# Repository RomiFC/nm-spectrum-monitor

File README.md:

# :satellite: New Mexico Spectrum Monitor

The NMSM is a tool utilized by the NRAO-NM Interference Protection Group to identify and locate RF interference at the Very Large Array. It combines two previously separate systems: the Radio Frequency - Direction Finding System (RF-DFS) and Environmental Monitoring System (RF-EMS) into one combined spectrum monitor with omnidirectional and directional capabilities. The former is a 3-meter dish antenna with azimuth and elevation drives whereas the latter is a 50-foot tower with a nominally 0 dBi club antenna. Both RF chains are connected to a Keysight N9040B Spectrum Analyzer and are controlled by a Python GUI.

**Hardware:** Automation Direct P1AM-100 PLC with 15-point discrete output module, Parker Hannifin ACR9000 Motion Controller, 2 Aries AR-04AE Servo Drives, Keysight N9040B Spectrum Analyzer, and a Windows computer.

## 🏗️ Tech Stack

```mermaid
graph BT

    subgraph Hardware
    P1AM
    win[Windows Machine]
    ACR9000
    AR-04AE
    N9040B
    end

    subgraph Firmware
    C++
    AcroBASIC
    SCPI
    end

    subgraph client[Edge Client]
    Python([Python Front End])
    end

    subgraph Back End
    Database[(DRIFT<br>Database)]
    end

    C++ -->|Serial| Python
    AcroBASIC -->|Serial| Python
    SCPI -->|GPIB/LAN| Python

    P1AM --> C++
    win --> Python
    ACR9000 & AR-04AE --> AcroBASIC
    N9040B --> SCPI
    client --> Database
```

## 🚀 Deployment Requirements

- [NI-VISA](https://www.ni.com/en/support/downloads/drivers/download.ni-visa.html) or other suitable PyVISA backend.
- Ethernet, GPIB, serial, or other SCPI instrument connection.
  - [NI-488.2](https://www.ni.com/en/support/downloads/drivers/download.ni-488-2.html#484357) if using GPIB.

## 🛠️ Development Requirements

- All above requirements.
- [Python 3.11+](https://www.python.org/) and an understanding of the following:
  - [tkinter](https://docs.python.org/3/library/tkinter.html#module-tkinter)
  - [pySerial](https://pypi.org/project/pyserial/)
  - [PyVisa](https://pyvisa.readthedocs.io/en/latest/)
  - [matplotlib](https://matplotlib.org/)
- Suitable Python IDE (Recommended [VSCode](https://code.visualstudio.com/))
- Python packager (Recommended [PyInstaller](https://pyinstaller.org/en/stable/))
- [PlatformIO](https://platformio.org/) for updating PLC firmware.

> [!NOTE]
> Freezing tools (Such as PyInstaller) package the entire Python Interpreter and installed libraries which generates large executables and could be flagged as a virus. It is recommended to create a virtual environment and only install/package the libraries used in the program. These executables will also only work on the OS that built them (A Windows deployment must be built on a Windows computer).

### Packages

```bash
pip install -r requirements.txt
```

## :mailbox: Authors

- [Remy Nguyen](https://github.com/RomiFC)
- [Natalie Ceonzo](https://github.com/nceonzo)
- [Hina Suzuki](https://github.com/hina18201716)

<picture>
  <source media="(prefers-color-scheme: dark)" srcset="https://public.nrao.edu/wp-content/uploads/2023/02/logoGroupWhite.png">
  <source media="(prefers-color-scheme: light)" srcset="https://public.nrao.edu/wp-content/uploads/2023/02/logoGroupColor.png">
  
</picture>

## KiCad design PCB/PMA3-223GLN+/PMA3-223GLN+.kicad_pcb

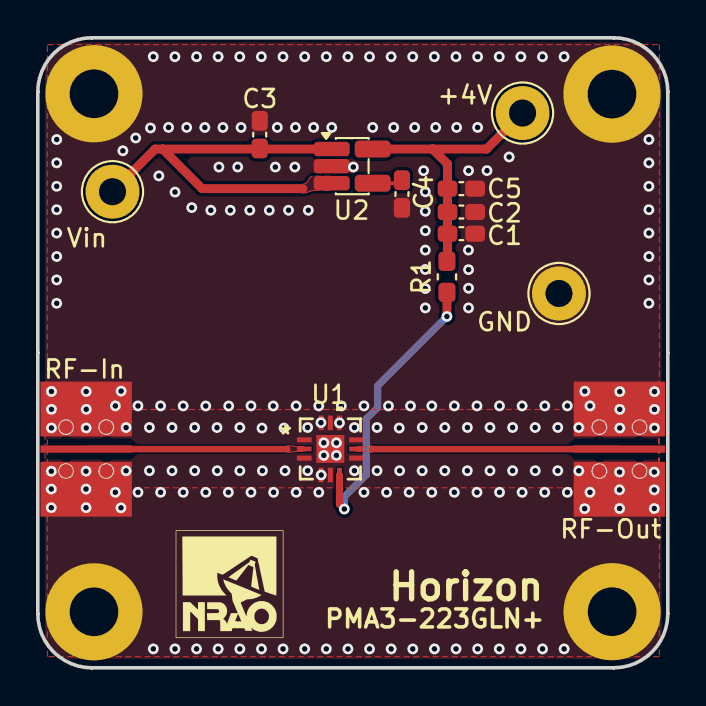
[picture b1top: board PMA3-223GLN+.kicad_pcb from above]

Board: 4 copper layers, 35.0 x 35.0 mm, 14 parts (0 on the bottom side), 7 nets.

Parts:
+4V: +4V; TestPoint_Loop_D2.54mm_Drill1.5mm_Beaded
C1: 5p; C_0402_1005Metric_Pad0.74x0.62mm_HandSolder
C2: 0.1u; C_0402_1005Metric_Pad0.74x0.62mm_HandSolder
C3: 1u; C_0402_1005Metric_Pad0.74x0.62mm_HandSolder
C4: 100p; C_0402_1005Metric_Pad0.74x0.62mm_HandSolder
C5: 2.2u; C_0402_1005Metric_Pad0.74x0.62mm_HandSolder
G**: NRAO Logo; nrao_logo_silk
GND: GND; TestPoint_Loop_D2.54mm_Drill1.5mm_Beaded
J1, J2: Conn_Coaxial; BU-1420761881
R1: 18; C_0603_1608Metric_Pad1.08x0.95mm_HandSolder
U1: PMA3-223GLN+; DQ1225_MNC
U2: AP2210N-4.0TRG1; SOT-23-5
Vin: Vin; TestPoint_Loop_D2.54mm_Drill1.5mm_Beaded

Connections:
+4V: +4V.1 (1_1), C1.1, C2.1, C5.1, R1.2, U2.5 (VOUT)
GND: C1.2, C2.2, C3.2, C4.2, C5.2, GND.1 (1_1), J1.2 (Ext), J2.2 (Ext), U1.1 (GND), U1.3 (GND), U1.4 (NC), U1.5 (NC), U1.7 (GND), U1.9 (GND), U1.10 (NC), U1.11 (NC), U1.12 (NC), U1.13 (PADDLE), U2.2 (GND)
unnamed: C4.1, U2.4 (BP)
RF_IN: J1.1 (In), U1.2 (RF-IN)
RF_OUT: J2.1 (In), U1.8 (RF-OUT/DC-IN)
VDC: C3.1, U2.1 (VIN), U2.3 (ON/~OFF), Vin.1 (1_1)
VDD: R1.1, U1.6 (VDD)

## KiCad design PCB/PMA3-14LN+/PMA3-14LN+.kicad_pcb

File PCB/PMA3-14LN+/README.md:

# PMA3-14LN+ Changelog

## Revision C - 6/8/2026

### Added

- New thermal via grid underneath U2 for temperature management
- Layer 2 DGS underneath L1,L2,C1,C2,C3,C4 as follows:
    - Shunts L1,L2,C3,C4: 0.60mm x 0.1mm (trace pad)
    - Series C1,C2: 1.5mm x 0.5mm

### Changed

- Changed mouting pad dimensions of L1,L2,C1,C2,C3,C4 to 0.56mm x 0.62mm rounded rectangle. Previous values:
    - Shunts L1,L2: 0.37mm x 0.72mm rounded rectangle (trace pad) and 0.59mm x 0.64mm rectangle (bias pad)
    - Series C1,C2: 0.56mm x 0.37mm rounded rectangle (both)
    - Shunts C3,C4: 0.37mm x 0.72mm (trace pad) and 0.56mm x 0.62mm (bias pad)
- Increased clearance around trace components from 0.2mm to 0.3mm

## Revision B - 10/24/2023

### Added

- More PTH vias around and directly under RF components.
- Another layer of via picketing around transmission line.
- Silkscreen revision indicator.
- Dimensioning to assembly drawing.

### Changed

- Removed Hammond 1554B compatibility due to difficulties in assembly and weatherproofing SMA connectors. Overall board is smaller at 35mm x 35mm.
- SMA Connectors replaced with Mueller BU-1420761881 which have an upper frequency of 26.5 GHz and better impedance matching at the landing.
- GCPW dimensions from w = 0.415mm, s = 0.6mm, to w = 0.37mm, s = 0.2mm and added 0.375mm taper from SMA clearance to GCPW clearance.

### Fixed

- C9 footprint now correctly matches schematic (0402 --> 1206).
- Moved SMA footprints closer to board edge to reduce filing prior to assembly.

## Revision A - 4/12/2023

### First revision 🎉🎉🎉

- Board is built to 4-layer OSHPark specifications
- This amplifier showed slightly lower gain than expected, rolling off quicker with frequency. This is likely due to the SMA connector landings which had a known impedance mismatch, resulting in a steep rolloff somewhere between 12 and 18 GHz.

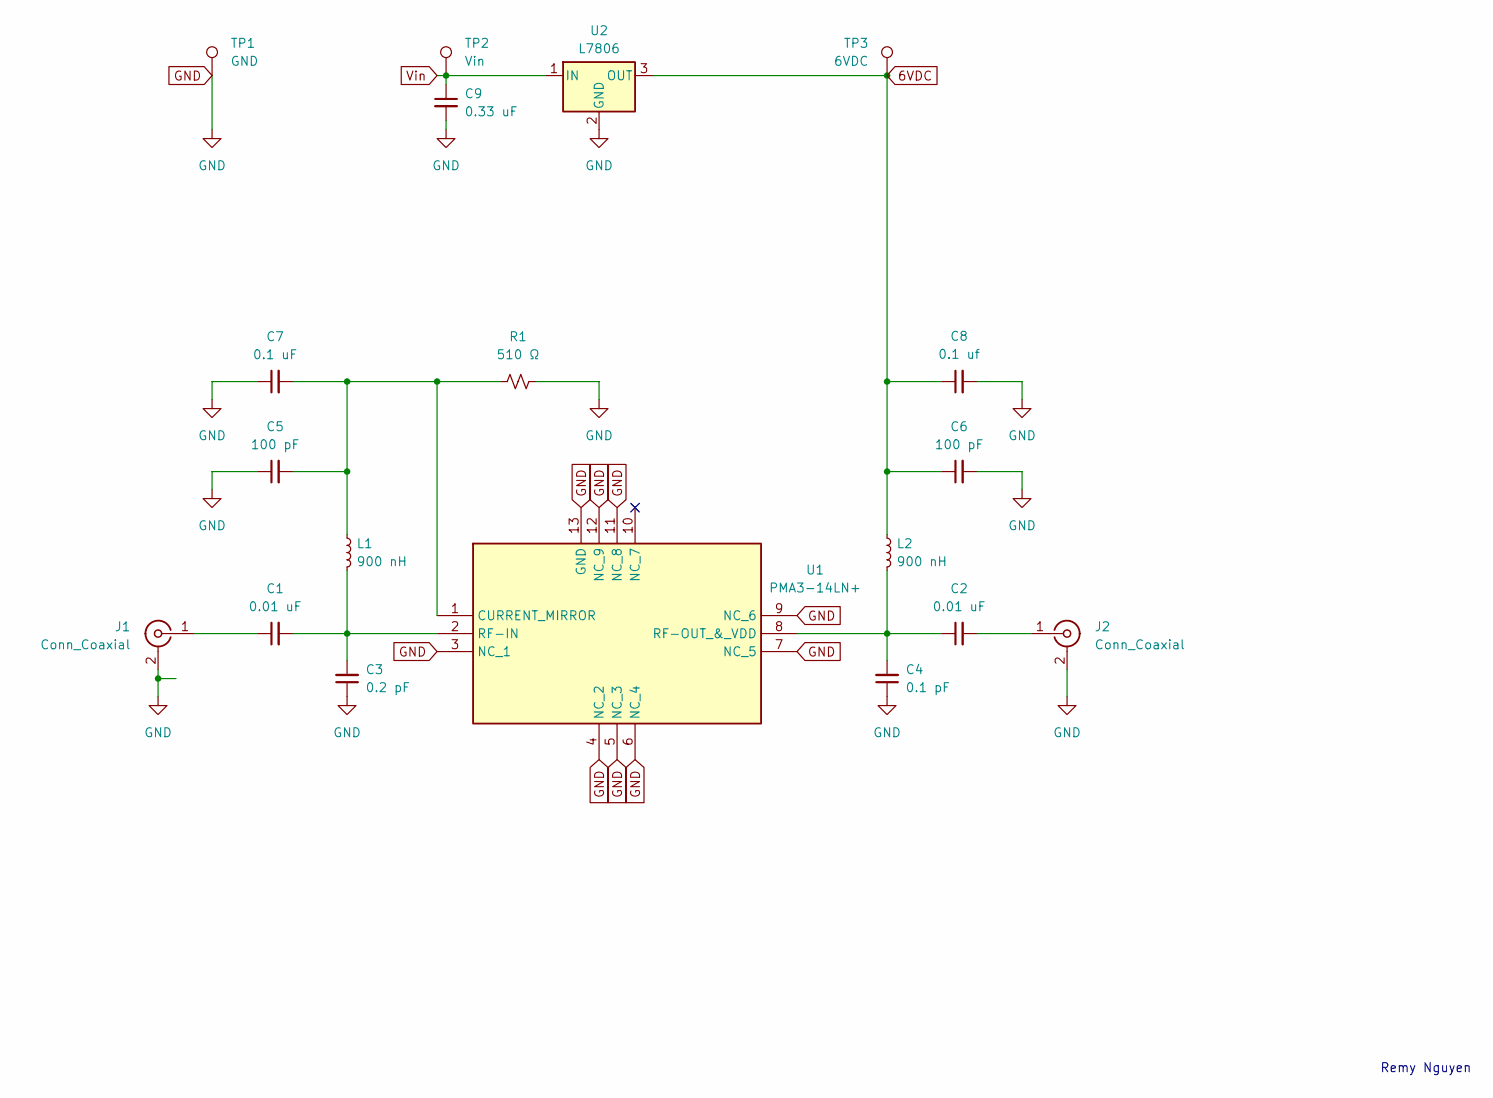
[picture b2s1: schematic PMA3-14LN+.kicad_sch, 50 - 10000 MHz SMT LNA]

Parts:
C1, C2: 0.01 uF; C_0402_1005Metric
C3: 0.2 pF; C_0402_1005Metric
C4: 0.1 pF; C_0402_1005Metric
C5, C6: 100 pF; C_0402_1005Metric
C7: 0.1 uF; C_0402_1005Metric
C8: 0.1 uf; C_0402_1005Metric
C9: 0.33 uF; C_0402_1005Metric
J1, J2: Conn_Coaxial; Mueller BU-1420761881-RevB
L1, L2: 900 nH; L_0402_1005Metric
R1: 510 Ω; R_0402_1005Metric
TP1: GND; TestPoint_Loop_D2.54mm_Drill1.5mm_Beaded
TP2: Vin; TestPoint_Loop_D2.54mm_Drill1.5mm_Beaded
TP3: 6VDC; TestPoint_Loop_D2.54mm_Drill1.5mm_Beaded
U1: PMA3-14LN+; QFN51P300X300X89-13N; Mouser Part Number 139-PMA3-14LN+
U2: L7806; TO-263-2

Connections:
6VDC: C6.1, C8.1, L2.1, TP3.1, U2.3 (OUT)
GND: C3.1, C4.1, C5.1, C6.2, C7.1, C8.2, C9.2, J1.2 (Ext), J2.2 (Ext), R1.2, TP1.1, U1.3 (NC_1), U1.4 (NC_2), U1.5 (NC_3), U1.6 (NC_4), U1.7 (NC_5), U1.9 (NC_6), U1.11 (NC_8), U1.12 (NC_9), U1.13 (GND), U2.2 (GND)
unnamed: C5.2, C7.2, L1.1, R1.1, U1.1 (CURRENT_MIRROR)
unnamed: C1.2, C3.2, L1.2, U1.2 (RF-IN)
unnamed: C2.1, C4.2, L2.2, U1.8 (RF-OUT_&_VDD)
unnamed: C1.1, J1.1 (In)
unnamed: C2.2, J2.1 (In)
Vin: C9.1, TP2.1, U2.1 (IN)

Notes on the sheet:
Remy Nguyen

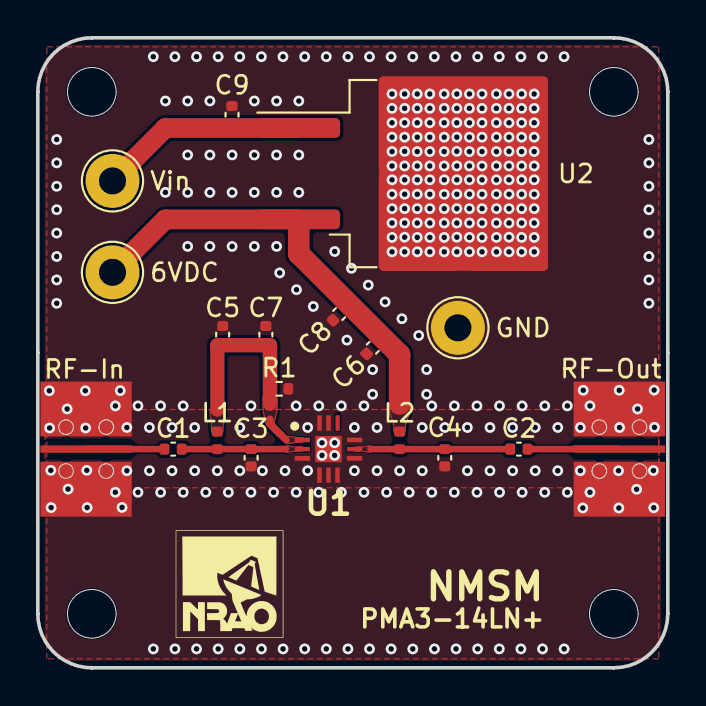
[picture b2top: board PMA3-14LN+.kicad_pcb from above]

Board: 4 copper layers, 35.0 x 35.0 mm, 20 parts (0 on the bottom side), 8 nets.

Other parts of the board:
 : FabDrawing-4Layer-Metric-Compact-OSH

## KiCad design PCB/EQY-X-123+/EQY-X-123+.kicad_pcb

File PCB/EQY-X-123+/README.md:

# EQY-X-123+ X-db Equalizer Changelog

## Revision A - 6/29/2026

### First revision 🎉🎉🎉

- Board is built to 4-layer OSHPark specifications
- Will update when board has been fabricated and assembled

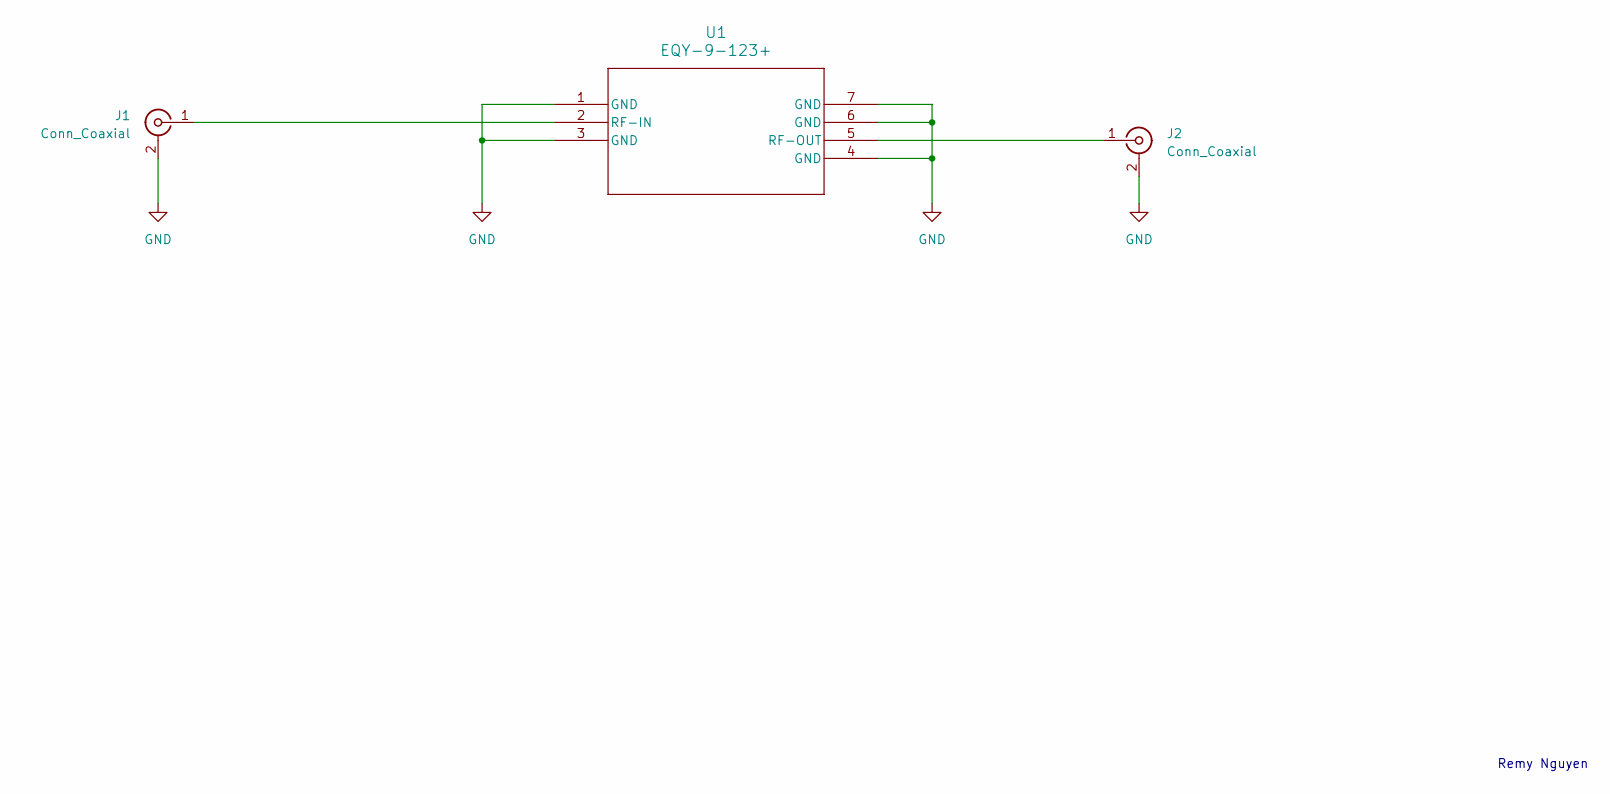
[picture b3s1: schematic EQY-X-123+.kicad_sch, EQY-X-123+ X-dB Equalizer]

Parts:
J1, J2: Conn_Coaxial; Mueller BU-1420761881-RevB
U1: EQY-9-123+; KC3011

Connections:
GND: J1.2 (Ext), J2.2 (Ext), U1.1 (GND), U1.3 (GND), U1.4 (GND), U1.6 (GND), U1.7 (GND)
unnamed: J1.1 (In), U1.2 (RF-IN)
unnamed: J2.1 (In), U1.5 (RF-OUT)

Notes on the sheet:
Remy Nguyen

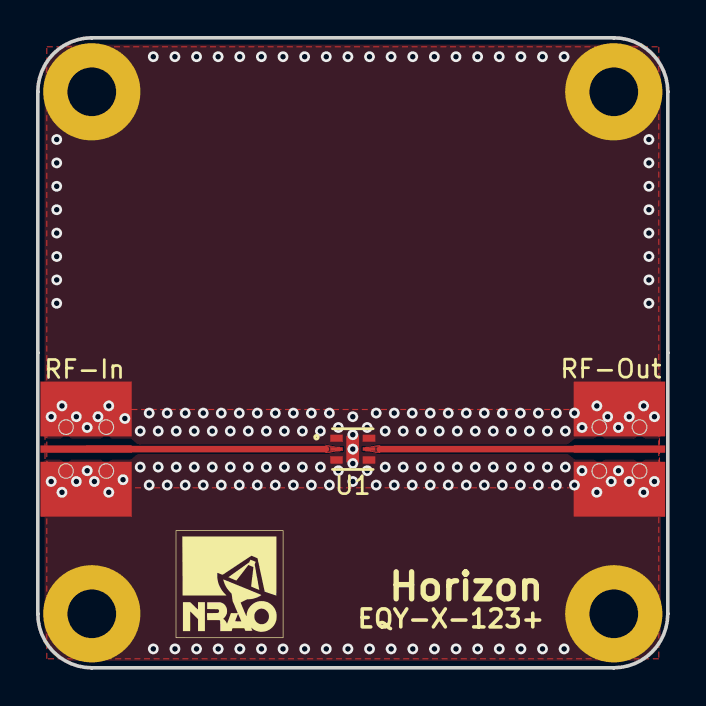
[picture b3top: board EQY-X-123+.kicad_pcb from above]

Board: 4 copper layers, 35.0 x 35.0 mm, 4 parts (0 on the bottom side), 3 nets.

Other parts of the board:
 : FabDrawing-4Layer-Metric-Compact-OSH

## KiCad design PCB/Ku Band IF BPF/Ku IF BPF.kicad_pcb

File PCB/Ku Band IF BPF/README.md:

# 1 - 9 GHz Bandpass Filter Changelog

## Revision A - 6/29/2026

### First revision 🎉🎉🎉

- Board is built to 4-layer OSHPark specifications
- Will update when board has been fabricated and assembled

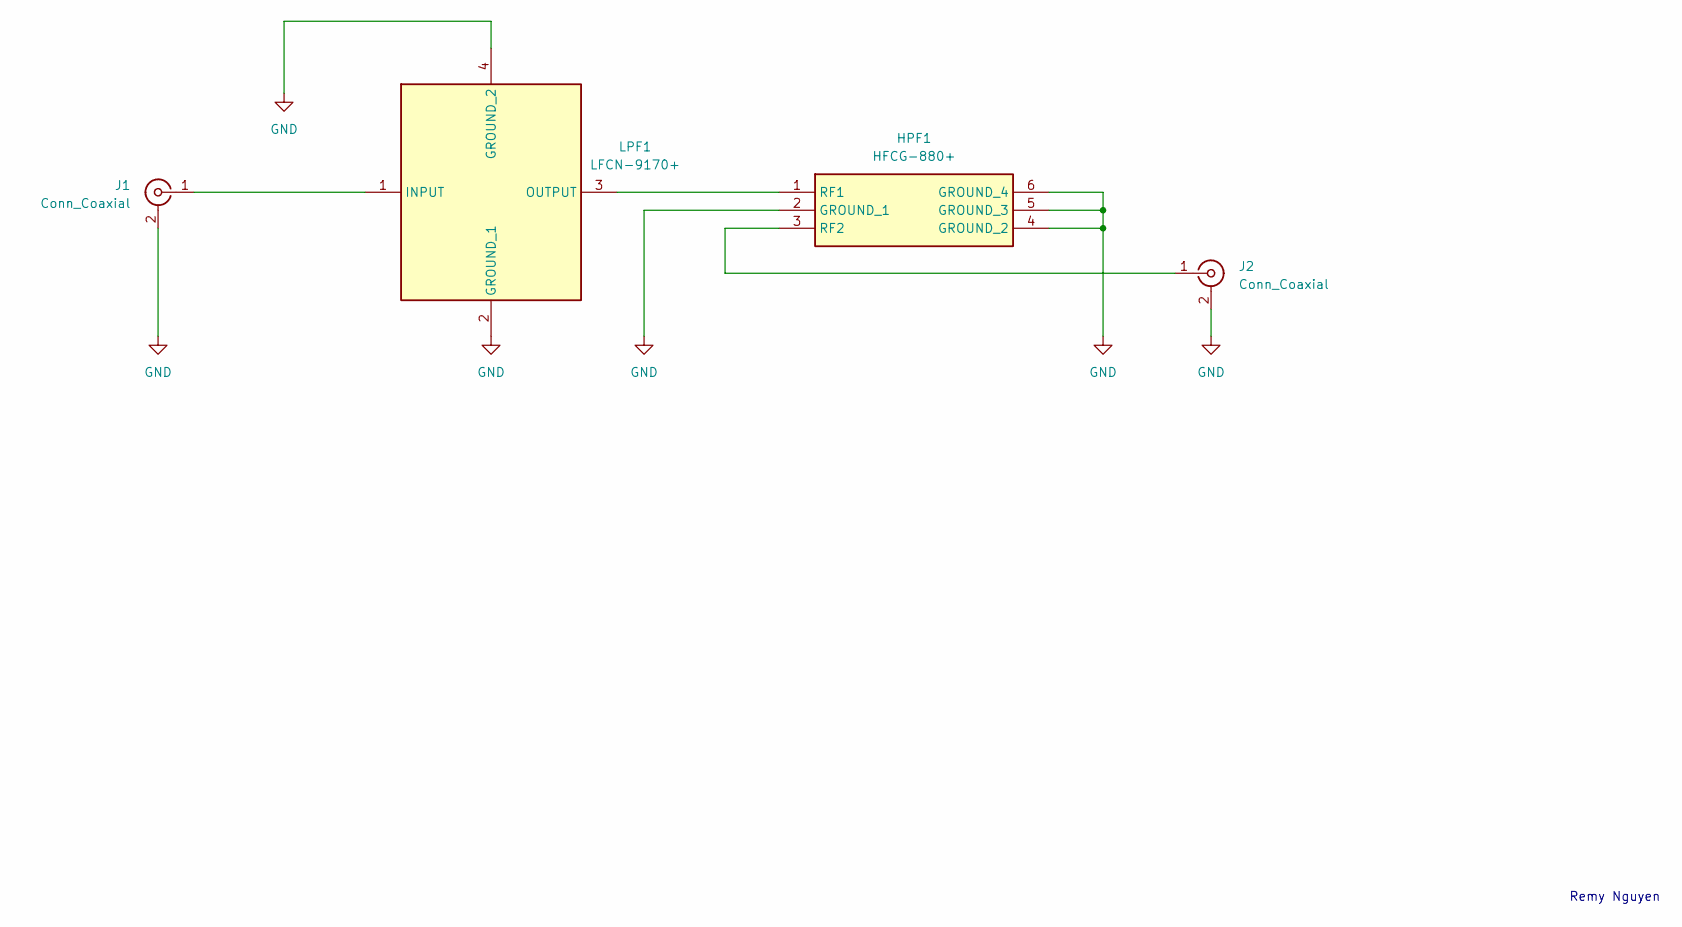
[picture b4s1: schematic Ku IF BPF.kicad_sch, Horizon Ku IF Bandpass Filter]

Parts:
HPF1: HFCG-880+; HFCG880; Mouser Part Number 139-HFCG-880+
J1, J2: Conn_Coaxial; Mueller BU-1420761881-RevB
LPF1: LFCN-9170+; LFCN9170; Mouser Part Number 139-LFCN-9170

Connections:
GND: HPF1.2 (GROUND_1), HPF1.4 (GROUND_2), HPF1.5 (GROUND_3), HPF1.6 (GROUND_4), J1.2 (Ext), J2.2 (Ext), LPF1.2 (GROUND_1), LPF1.4 (GROUND_2)
unnamed: HPF1.1 (RF1), LPF1.3 (OUTPUT)
unnamed: HPF1.3 (RF2), J2.1 (In)
unnamed: J1.1 (In), LPF1.1 (INPUT)

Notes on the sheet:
Remy Nguyen

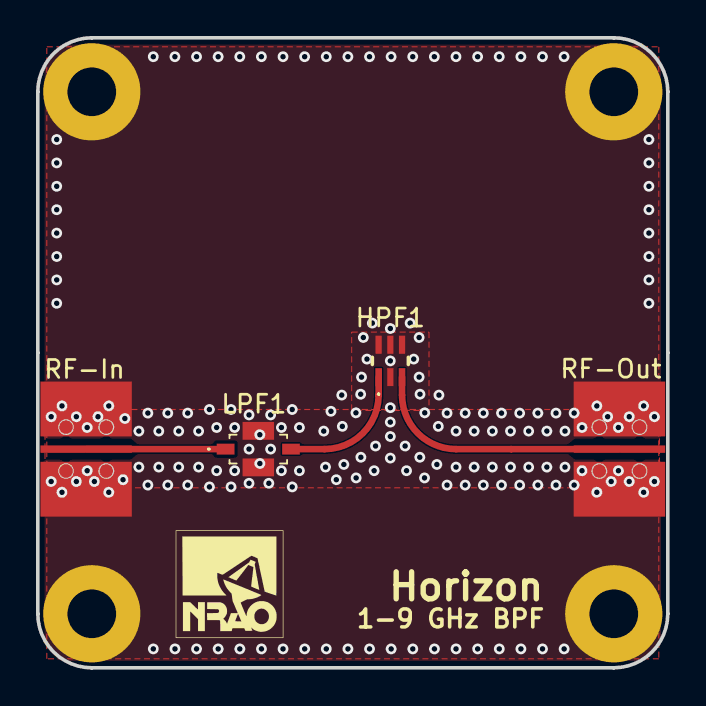
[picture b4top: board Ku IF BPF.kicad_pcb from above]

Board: 4 copper layers, 35.0 x 35.0 mm, 5 parts (0 on the bottom side), 4 nets.

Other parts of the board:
 : FabDrawing-4Layer-Metric-Compact-OSH

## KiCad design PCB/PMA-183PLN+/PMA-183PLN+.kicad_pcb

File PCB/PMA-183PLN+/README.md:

# PMA-183PLN+ Changelog

## Revision B - 7/5/2023

### Added

- More PTH vias around and directly under RF components.
- Another layer of via picketing around transmission line.
- Silkscreen revision indicator.
- Dimensioning to assembly drawing.

### Changed

- Removed Hammond 1554B compatibility due to difficulties in assembly and weatherproofing SMA connectors.
- GCPW dimensions from w = 0.41mm, s = 0.2mm, to w = 0.37mm, s = 0.2mm and added 0.375mm taper from SMA clearance to GCPW clearance.

### Fixed

- C9 footprint now correctly matches schematic (0402 --> 1206).
- Moved SMA footprints closer to board edge to reduce filing prior to assembly.

## Revision A - 6/12/2023

### First revision 🎉🎉🎉

- Board is built to 4-layer OSHPark specifications
- Testing shows amplifier oscillates strongly at ~18.5 GHz. This occurs both when the amplifier is biased through the regulator or directly from a DC power supply. SMA landings were also copied from test coupons so that can likely be ruled out. This is possibly due to the lack of PTH vias directly under the IC or the tuning/spacing of picketing around the transmission line.

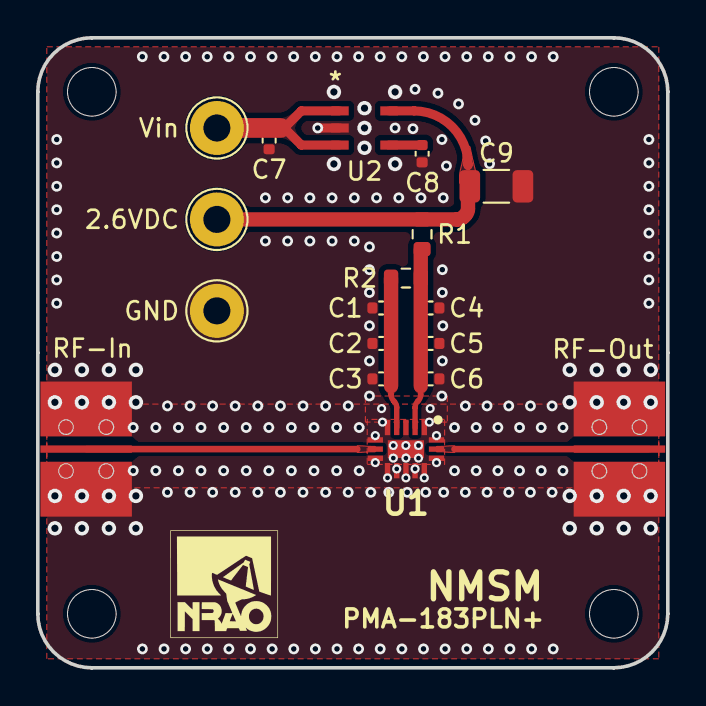
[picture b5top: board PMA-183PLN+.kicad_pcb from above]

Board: 4 copper layers, 35.0 x 35.0 mm, 20 parts (0 on the bottom side), 8 nets.

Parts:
 : FabDrawing-4Layer-Metric-Compact-OSH
 #2: LOGO; GCPW_osh3_90mm_user
C1, C4, C7: 0.33 uF; C_0402_1005Metric
C2, C5: 1000 pF; C_0402_1005Metric
C3, C6: 100 pF; C_0402_1005Metric
C8: 470 pF; C_0402_1005Metric
C9: 2.2 uF; C_1206_3216Metric
J1, J2: Conn_Coaxial; Mueller BU-1420761881
R1: 10 Ω; R_0603_1608Metric
R2: 180 Ω; R_0603_1608Metric
TP1: GND; TestPoint_Loop_D2.54mm_Drill1.5mm_Beaded
TP2: Vin; TestPoint_Loop_D2.54mm_Drill1.5mm_Beaded
TP3: 2.6VDC; TestPoint_Loop_D2.54mm_Drill1.5mm_Beaded
U1: PMA-183PLN+; QFN51P250X350X85-17N
U2: MIC5219-2.6YM5-TR; SOT-23-5_M5_MCH

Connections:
2.6VDC: C9.1, R1.2, TP3.1, U2.5 (OUT)
GND: C1.1, C2.1, C3.1, C4.2, C5.2, C6.2, C7.2, C8.2, C9.2, J1.2 (Ext), J2.2 (Ext), TP1.1, U1.1 (NC_1), U1.3 (NC_2), U1.5 (NC_3), U1.6 (GND_1), U1.8 (GND_2), U1.9 (NC_4), U1.10 (NC_5), U1.11 (NC_6), U1.12 (NC_7), U1.13 (NC_8), U1.14 (GND_3), U1.16 (GND_4), U1.17 (EP), U2.2 (GND)
unnamed: J1.1 (In), U1.7 (RF-IN)
unnamed: J2.1 (In), U1.15 (RF-OUT)
unnamed: C4.1, C5.1, C6.1, R1.1, R2.2, U1.2 (VDD)
unnamed: C1.2, C2.2, C3.2, R2.1, U1.4 (VE)
unnamed: C8.1, U2.4 (BYP)
Vin: C7.1, TP2.1, U2.1 (IN), U2.3 (EN)

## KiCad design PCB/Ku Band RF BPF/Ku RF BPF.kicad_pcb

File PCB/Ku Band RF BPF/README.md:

# 10 - 18 GHz Bandpass Filter Changelog

## Revision A - 6/29/2026

### First revision 🎉🎉🎉

- Board is built to 4-layer OSHPark specifications
- Will update when board has been fabricated and assembled

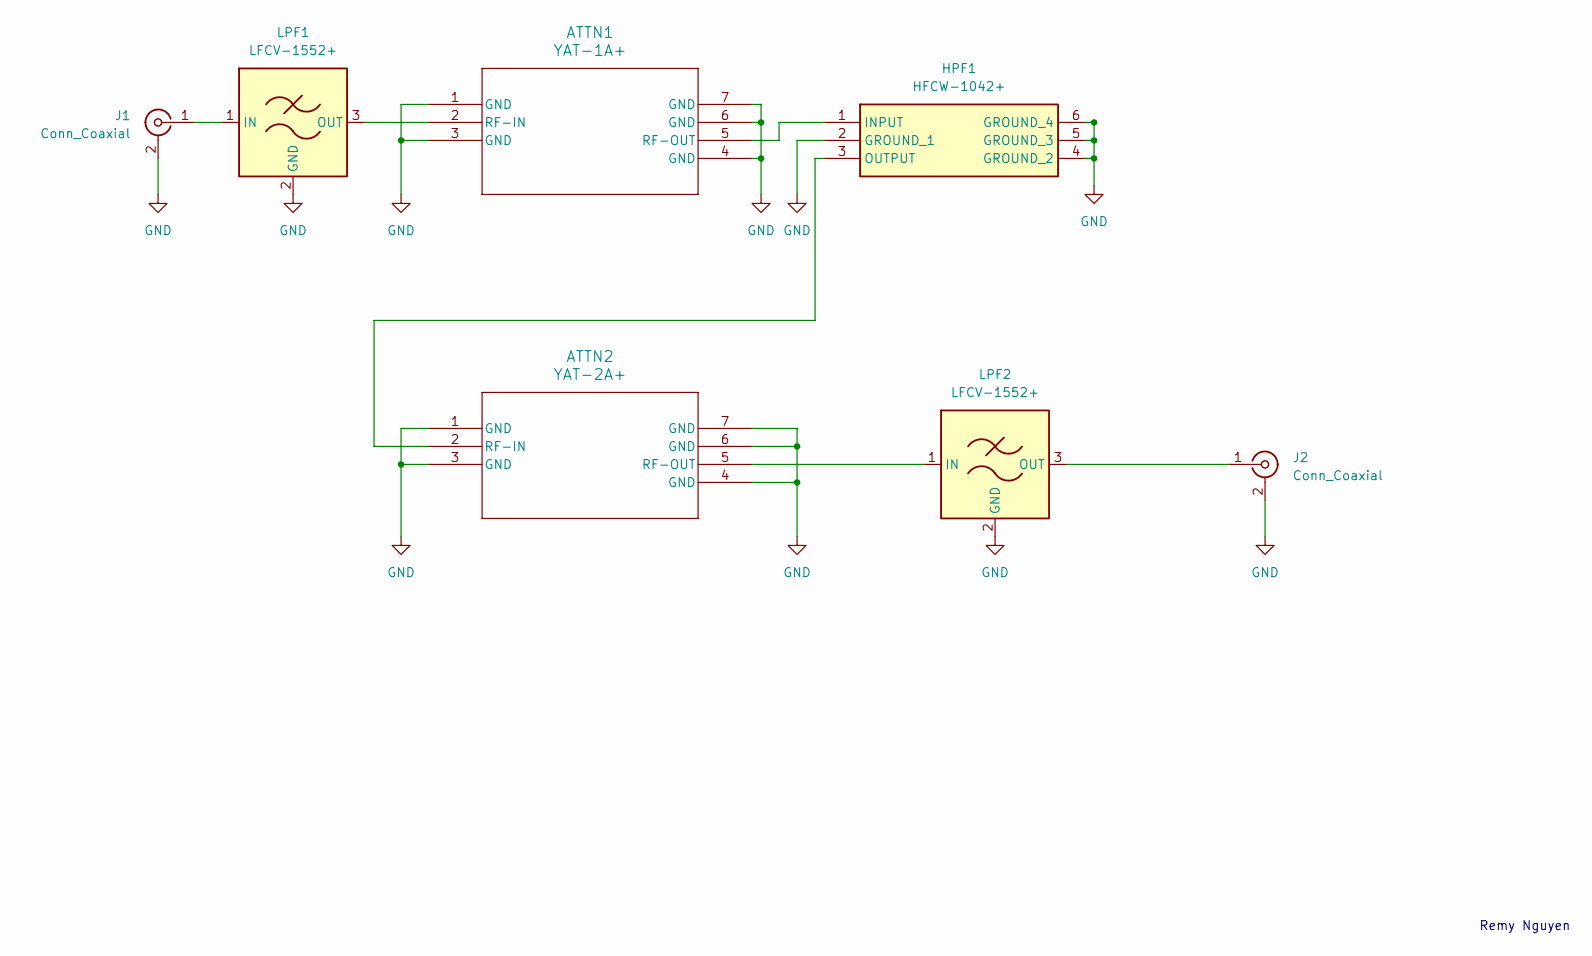
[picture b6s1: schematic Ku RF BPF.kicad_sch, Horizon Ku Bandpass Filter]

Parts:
ATTN1: YAT-1A+; MC1630_MNC
ATTN2: YAT-2A+; MC1630_MNC
HPF1: HFCW-1042+; HFCW1042; Mouser Part Number 139-HFCW-1042+
J1, J2: Conn_Coaxial; Mueller BU-1420761881-RevB
LPF1, LPF2: LFCV-1552+; Filter_Mini-Circuits_JV1210C-7

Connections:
GND: ATTN1.1 (GND), ATTN1.3 (GND), ATTN1.4 (GND), ATTN1.6 (GND), ATTN1.7 (GND), ATTN2.1 (GND), ATTN2.3 (GND), ATTN2.4 (GND), ATTN2.6 (GND), ATTN2.7 (GND), HPF1.2 (GROUND_1), HPF1.4 (GROUND_2), HPF1.5 (GROUND_3), HPF1.6 (GROUND_4), J1.2 (Ext), J2.2 (Ext), LPF1.2 (GND), LPF2.2 (GND)
unnamed: ATTN1.2 (RF-IN), LPF1.3 (OUT)
unnamed: ATTN1.5 (RF-OUT), HPF1.1 (INPUT)
unnamed: ATTN2.2 (RF-IN), HPF1.3 (OUTPUT)
unnamed: ATTN2.5 (RF-OUT), LPF2.1 (IN)
unnamed: J1.1 (In), LPF1.1 (IN)
unnamed: J2.1 (In), LPF2.3 (OUT)

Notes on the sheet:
Remy Nguyen

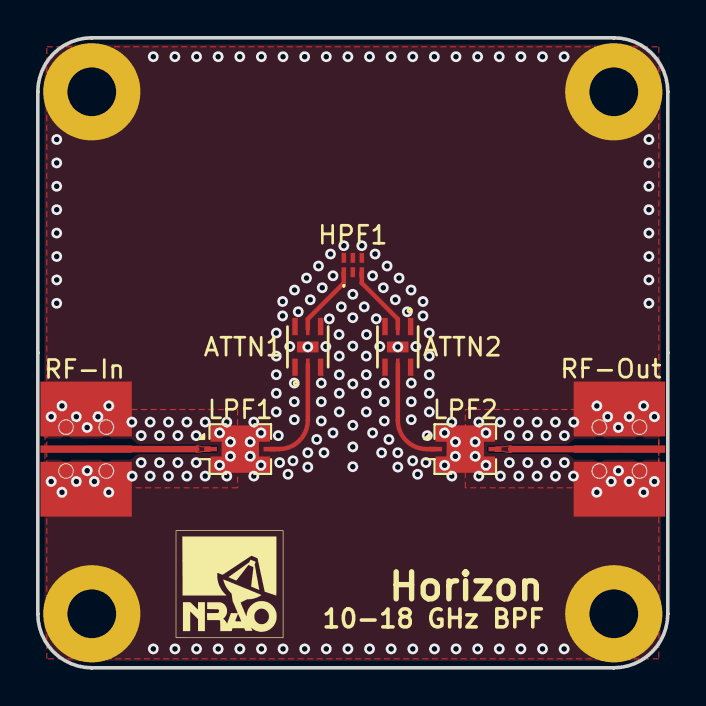
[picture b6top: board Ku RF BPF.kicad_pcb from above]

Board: 4 copper layers, 35.0 x 35.0 mm, 8 parts (0 on the bottom side), 7 nets.

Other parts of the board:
 : FabDrawing-4Layer-Metric-Compact-OSH

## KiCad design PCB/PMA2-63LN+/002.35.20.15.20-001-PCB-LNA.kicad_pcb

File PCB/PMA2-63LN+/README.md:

# PMA2-63LN+ Changelog

## Revision C - 2/23/2024

### Added

- SMA connectors dimensioned.

### Changed

- Drawing sheets changed from A4 to Letter size.
- New stackup table format.

### Fixed

- SMA launch pad widened with ground plane cutout to improve Z-matching.
- Mounting holes now correctly part of GND net.

## Revision B - 1/23/2024

### Added

- GCPW cross-section to assembly drawing.
- Board characteristics to assembly drawing.
- Board dimensioning to assembly drawing.
- Test points for DC power as an alternative to SMA.
- Test points for Iadj control.
- More PTH vias around and directly under RF components.
- Layer indicator to top left of assembly drawing.

### Changed

- Stackup changed from 2-layer, 30 mil RO4350b to 4-layer OSHPark specifications.
- Board compacted in attempt to reduce oscillations from quarter-wave resonance.
- Connector references changed from J- to more descriptive names.

### Fixed

- Removed back mask from linear regulator pads to improve thermal conductance.
- Iadj resistor to ground replaced with voltage divider for control from +5VDC to GND.

## Revision A - 7/6/2023

### First revision 🎉🎉🎉

- Board is built on 30-mil Rogers RO4350b with 2 layers. Contains two LNAs with their own linear regulators and a 1 dB attenuator between them to improve return loss.
- Testing shows amplifier instability/oscillations at ~10.8 GHz with both PMA2-63LN+ and PMA2-123LN+. This was caused by shunt capacitance introduced from the relatively large SMA landing pads and Molex center conductor.
- 30-mil substrate proved to be thin and more prone to breakage/flexing, especially when torquing SMA connectors.

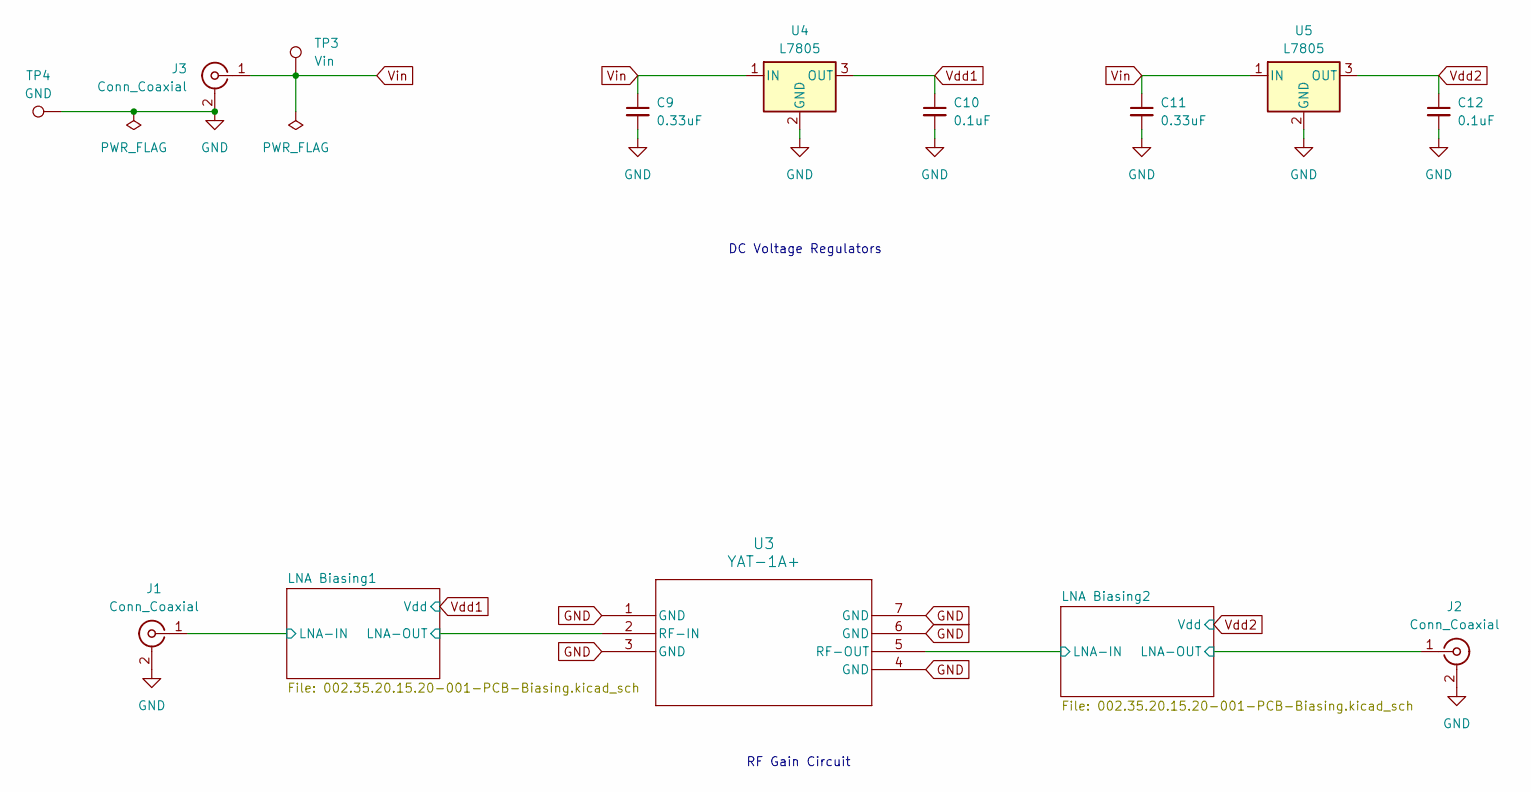
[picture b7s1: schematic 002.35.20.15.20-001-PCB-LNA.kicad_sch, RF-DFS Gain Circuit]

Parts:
C9, C11: 0.33uF; C_0402_1005Metric
C10, C12: 0.1uF; C_0402_1005Metric
J1, J2, J3: Conn_Coaxial; SMA_Molex_73251-1153_EdgeMount_Horizontal
TP3: Vin; TestPoint_Loop_D2.54mm_Drill1.5mm_Beaded
TP4: GND; TestPoint_Loop_D2.54mm_Drill1.5mm_Beaded
U3: YAT-1A+; MC1630_MNC
U4, U5: L7805; TO-263-2

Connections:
/LNA Biasing1/LNA-IN: J1.1 (In); also elsewhere on the board
/LNA Biasing1/LNA-OUT: U3.2 (RF-IN); also elsewhere on the board
/LNA Biasing2/LNA-IN: U3.5 (RF-OUT); also elsewhere on the board
/LNA Biasing2/LNA-OUT: J2.1 (In); also elsewhere on the board
GND: C9.2, C10.2, C11.2, C12.2, J1.2 (Ext), J2.2 (Ext), J3.2 (Ext), TP4.1, U3.1 (GND), U3.3 (GND), U3.4 (GND), U3.6 (GND), U3.7 (GND), U4.2 (GND), U5.2 (GND); also elsewhere on the board
Vdd1: C10.1, U4.3 (OUT); also elsewhere on the board
Vdd2: C12.1, U5.3 (OUT); also elsewhere on the board
Vin: C9.1, C11.1, J3.1 (In), TP3.1, U4.1 (IN), U5.1 (IN)

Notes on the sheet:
RF Gain Circuit
DC Voltage Regulators

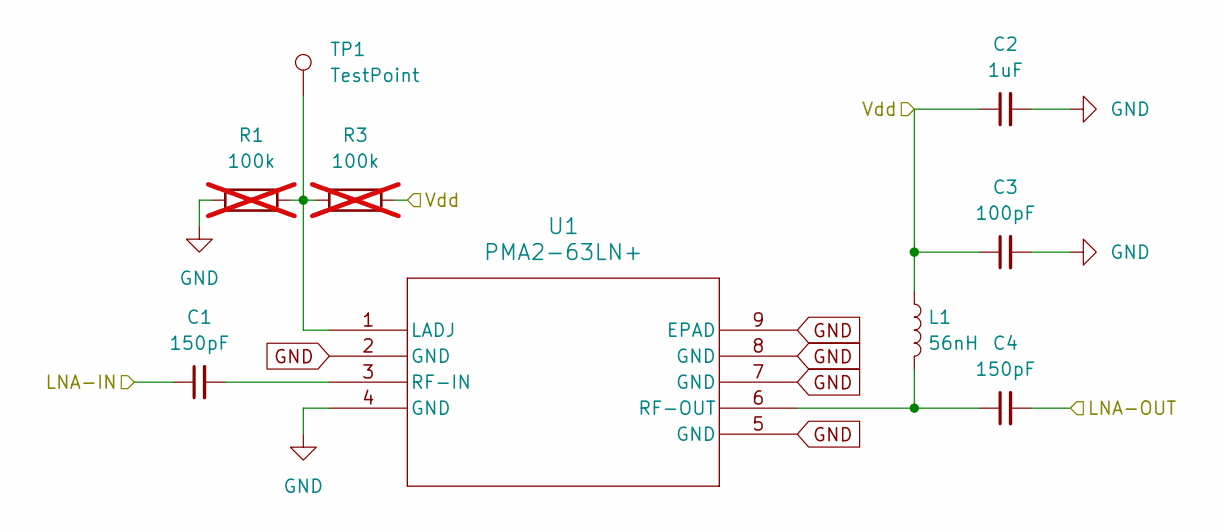
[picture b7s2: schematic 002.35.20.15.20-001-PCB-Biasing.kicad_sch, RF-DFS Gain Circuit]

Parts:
C1, C4: 150pF; C_0402_1005Metric
C2: 1uF; C_0402_1005Metric
C3: 100pF; C_0402_1005Metric
L1: 56nH; L_0402_1005Metric
R1, R3: 100k; R_0402_1005Metric; not fitted
TP1: TestPoint; TestPoint_Loop_D2.54mm_Drill1.5mm_Beaded
U1: PMA2-63LN+; SON8_PMA2_MNC

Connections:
/LNA Biasing1/LNA-IN: C1.1; also elsewhere on the board
/LNA Biasing1/LNA-OUT: C4.2; also elsewhere on the board
GND: C2.2, C3.2, R1.1, U1.2 (GND), U1.4 (GND), U1.5 (GND), U1.7 (GND), U1.8 (GND), U1.9 (EPAD); also elsewhere on the board
unnamed: R1.2, R3.1, TP1.1, U1.1 (LADJ)
unnamed: C1.2, U1.3 (RF-IN)
unnamed: C4.1, L1.2, U1.6 (RF-OUT)
Vdd1: C2.1, C3.1, L1.1, R3.2; also elsewhere on the board

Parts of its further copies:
C5, C8: 150pF; C_0402_1005Metric
C6: 1uF; C_0402_1005Metric
C7: 100pF; C_0402_1005Metric
L2: 56nH; L_0402_1005Metric
R2, R4: 100k; R_0402_1005Metric; not fitted
TP2: TestPoint; TestPoint_Loop_D2.54mm_Drill1.5mm_Beaded
U2: PMA2-63LN+; SON8_PMA2_MNC

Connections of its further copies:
/LNA Biasing2/LNA-IN: C5.1; also elsewhere on the board
/LNA Biasing2/LNA-OUT: C8.2; also elsewhere on the board
GND: C6.2, C7.2, R2.1, U2.2 (GND), U2.4 (GND), U2.5 (GND), U2.7 (GND), U2.8 (GND), U2.9 (EPAD); also elsewhere on the board
unnamed: R2.2, R4.1, TP2.1, U2.1 (LADJ)
unnamed: C5.2, U2.3 (RF-IN)
unnamed: C8.1, L2.2, U2.6 (RF-OUT)
Vdd2: C6.1, C7.1, L2.1, R4.2; also elsewhere on the board

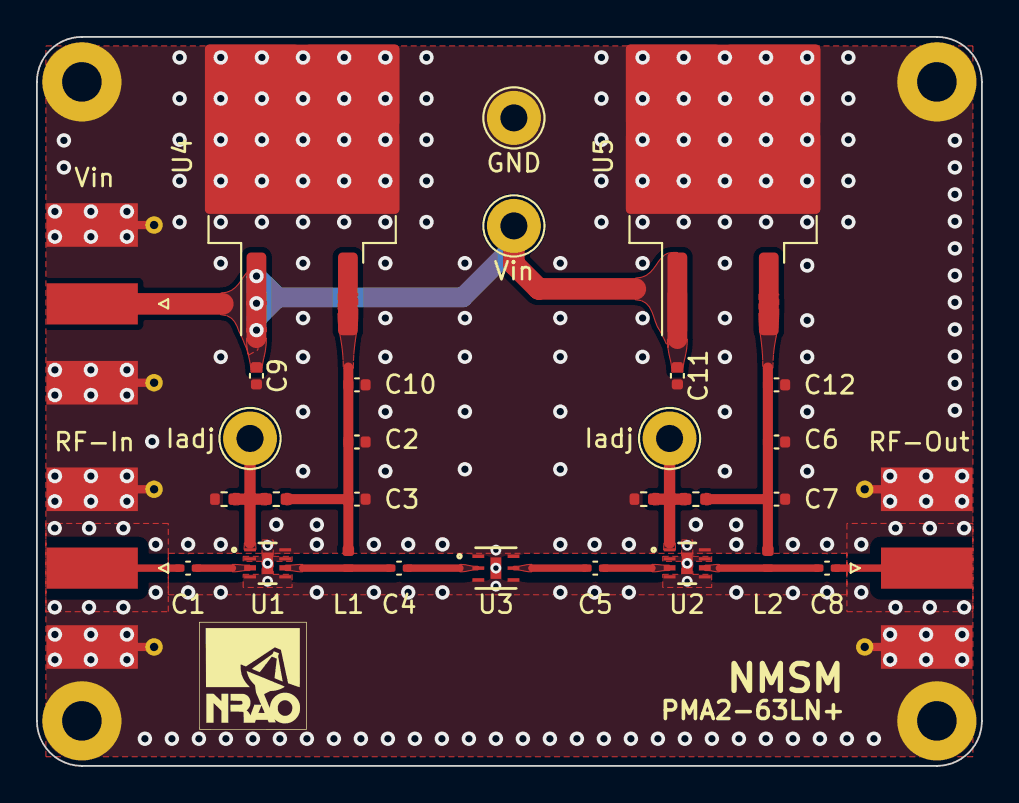
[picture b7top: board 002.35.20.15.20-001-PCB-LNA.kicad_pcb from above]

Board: 4 copper layers, 52.5 x 40.5 mm, 30 parts (0 on the bottom side), 14 nets.

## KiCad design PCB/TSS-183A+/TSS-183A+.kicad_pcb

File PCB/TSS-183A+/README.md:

# TSS-183A+ Changelog

## Revision A - 5/30/2024

- Not showing gain, S21 and S12 are perfectly reciprocal.

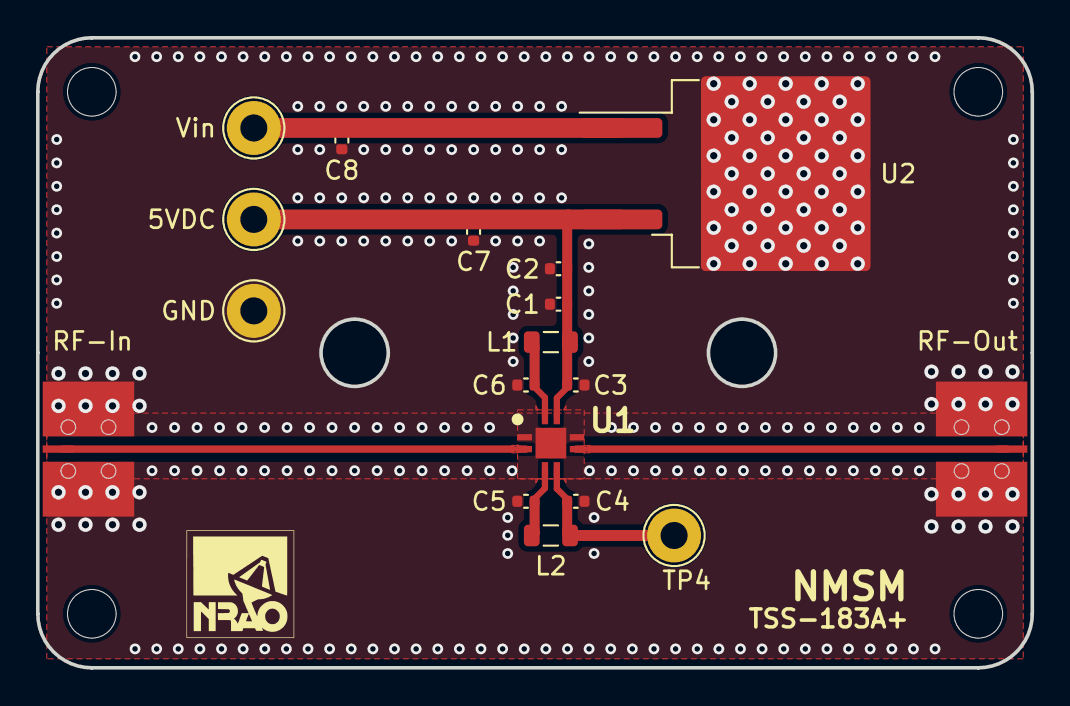
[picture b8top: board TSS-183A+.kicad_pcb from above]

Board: 4 copper layers, 55.3 x 35.0 mm, 20 parts (0 on the bottom side), 8 nets.

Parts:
5VDC: 5VDC; TestPoint_Loop_D2.54mm_Drill1.5mm_Beaded
 : LOGO; GCPW_osh2_90mm_user
 #2: FabDrawing-4Layer-Metric-Compact-OSH
C1: 5.6 pF; C_0402_1005Metric
C2: 18 pF; C_0402_1005Metric
C3, C4, C5: 1 nF; C_0402_1005Metric
C6, C7: 0.1 uF; C_0402_1005Metric
C8: 0.33 uF; C_0402_1005Metric
GND: GND; TestPoint_Loop_D2.54mm_Drill1.5mm_Beaded
L1, L2: 3.3 nH; L_0805_2012Metric
RF-In: Conn_Coaxial; Mueller BU-1420761881
RF-Out: Conn_Coaxial; Mueller BU-1420761881
TP4: Vg; TestPoint_Loop_D2.54mm_Drill1.5mm_Beaded
U1: TSS-183A+; QFN66P300X300X89-9N
U2: L7805; TO-263-2
Vin: Vin; TestPoint_Loop_D2.54mm_Drill1.5mm_Beaded

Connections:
5VDC: 5VDC.1, C1.1, C2.1, C3.1, C7.1, L1.1, U1.7 (VDD2), U2.3 (OUT)
GND: C1.2, C2.2, C3.2, C4.1, C5.2, C6.1, C7.2, C8.2, GND.1, RF-In.2 (Ext), RF-Out.2 (Ext), U1.1 (NC_1), U1.6 (NC_2), U1.9 (EP), U2.2 (GND)
unnamed: RF-In.1 (In), U1.2 (RF-IN)
unnamed: RF-Out.1 (In), U1.5 (RF-OUT)
unnamed: C6.2, L1.2, U1.8 (VDD1)
unnamed: C5.1, L2.1, U1.3 (VG1)
unnamed: C4.2, L2.2, TP4.1, U1.4 (VG2)
Vin: C8.1, U2.1 (IN), Vin.1
